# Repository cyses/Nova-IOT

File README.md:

<!DOCTYPE html><html><head><meta charset="utf-8"></head><body id="preview">
<h1 class="code-line" data-line-start=0 data-line-end=1>NovaIoT Cookbook</h1>

<p class="has-line-data" data-line-start="5" data-line-end="6">NovaIoT is an open-source framework that is made for spreading LoRa Sensors all over the world. NovaIoT package consists of two main parts:</p>
<ul>
<li class="has-line-data" data-line-start="6" data-line-end="7">The Hardware design for LoRa modules</li>
<li class="has-line-data" data-line-start="7" data-line-end="8">The Software design for LoRa sensors.</li>
<li class="has-line-data" data-line-start="8" data-line-end="10">And a little bit Magic :)</li>
</ul>
<h1 class="code-line" data-line-start=10 data-line-end=11>New Features!</h1>
<ul>

<li class="has-line-data" data-line-start="12" data-line-end="13">You can visualize the sensor data in the GUI app with a RestFull API.</li>
</ul>
<p class="has-line-data" data-line-start="16" data-line-end="17">You can also:</p>
<ul>
<li class="has-line-data" data-line-start="17" data-line-end="18">Use the hardware design and print the PCB.</li>
<li class="has-line-data" data-line-start="18" data-line-end="19">With required components for PCB you can complete the sensor at all.</li>
<li class="has-line-data" data-line-start="19" data-line-end="20">You can use any IP67 case for the sensor. (We are going to upload the IP67 design soon if you want to use a ready one!)</li>
<li class="has-line-data" data-line-start="20" data-line-end="21">You can integrate the sensor on our server software. (which would be online soon!)</li>
<li class="has-line-data" data-line-start="21" data-line-end="22">You can use our GUI in order to visualize the sensor data (just think like mqtt)</li>
</ul>
<p class="has-line-data" data-line-start="24" data-line-end="25">Here there are several things that we need to mention before we start!</p>
<blockquote>
<p class="has-line-data" data-line-start="26" data-line-end="32">Our primer aim is to spread this LoRa sensors all over the world fastly.<br>
We really believe in the power of open-source<br>
and we are always open to commits and suggestions!<br>
Please feel free if you have an idea for making any of these technologies better<br>
We are ready to hear and make the system better!<br>
or if you just want to use the design, you are very welcome. But do not forget that, it is free for NON-COMMERCIAL use!</p>
</blockquote>
<h3 class="code-line" data-line-start=34 data-line-end=35>Tech</h3>
<p class="has-line-data" data-line-start="36" data-line-end="37">First lets mention what components should you use. The components in the lists required very hard work and took a lot of time in order to find them.</p>
<ul>
<li class="has-line-data" data-line-start="38" data-line-end="39">STM32L072CZT6 - The main microprocessor that we used in our PCB</li>
<li class="has-line-data" data-line-start="39" data-line-end="40">SX1276IMLTRT - the core component for LoRa</li>
<li class="has-line-data" data-line-start="40" data-line-end="41">Li/SOCL2 4000 mAH 3.6v connector 2.54mm Two batteries side by side with protection - this is the magic battery. :)</li>
<li class="has-line-data" data-line-start="41" data-line-end="42">RFM95W-868 - the integrated LoRa module</li>
</ul>
<h3 class="code-line" data-line-start=45 data-line-end=46>Installation</h3>
<p class="has-line-data" data-line-start="47" data-line-end="49">We are changing our software infrastructure in docker based containers. But of course that would take time. Until that time you can use our PHP applications for GUI and server. You can ask us anything if you tackle in somewhere.<br>
The requirements for now are;</p>
<ul>
<li class="has-line-data" data-line-start="50" data-line-end="51">PHP 7.2 +</li>
<li class="has-line-data" data-line-start="51" data-line-end="52">Apache</li>
<li class="has-line-data" data-line-start="52" data-line-end="53">MySQL</li>
</ul>
After completing the setup of docker infrastructure, you would be run the environment as
<pre><code class="has-line-data" data-line-start="56" data-line-end="60" class="language-sh">$ <span class="hljs-built_in">docker</span> compose up

</code></pre>
<h3 class="code-line" data-line-start=63 data-line-end=64>Todos</h3>
<ul>
<li class="has-line-data" data-line-start="65" data-line-end="66"><em>Docker container</em></li>
<li class="has-line-data" data-line-start="66" data-line-end="68">Improvements in hardware design in order to make the PCB smaller</li>
</ul>
<h2 class="code-line" data-line-start=68 data-line-end=70>License</h2>
<p class="has-line-data" data-line-start="71" data-line-end="72">MIT</p>
<p class="has-line-data" data-line-start="74" data-line-end="75"><strong>Free Software, Hell Yeah!</strong></p>
</body></html>

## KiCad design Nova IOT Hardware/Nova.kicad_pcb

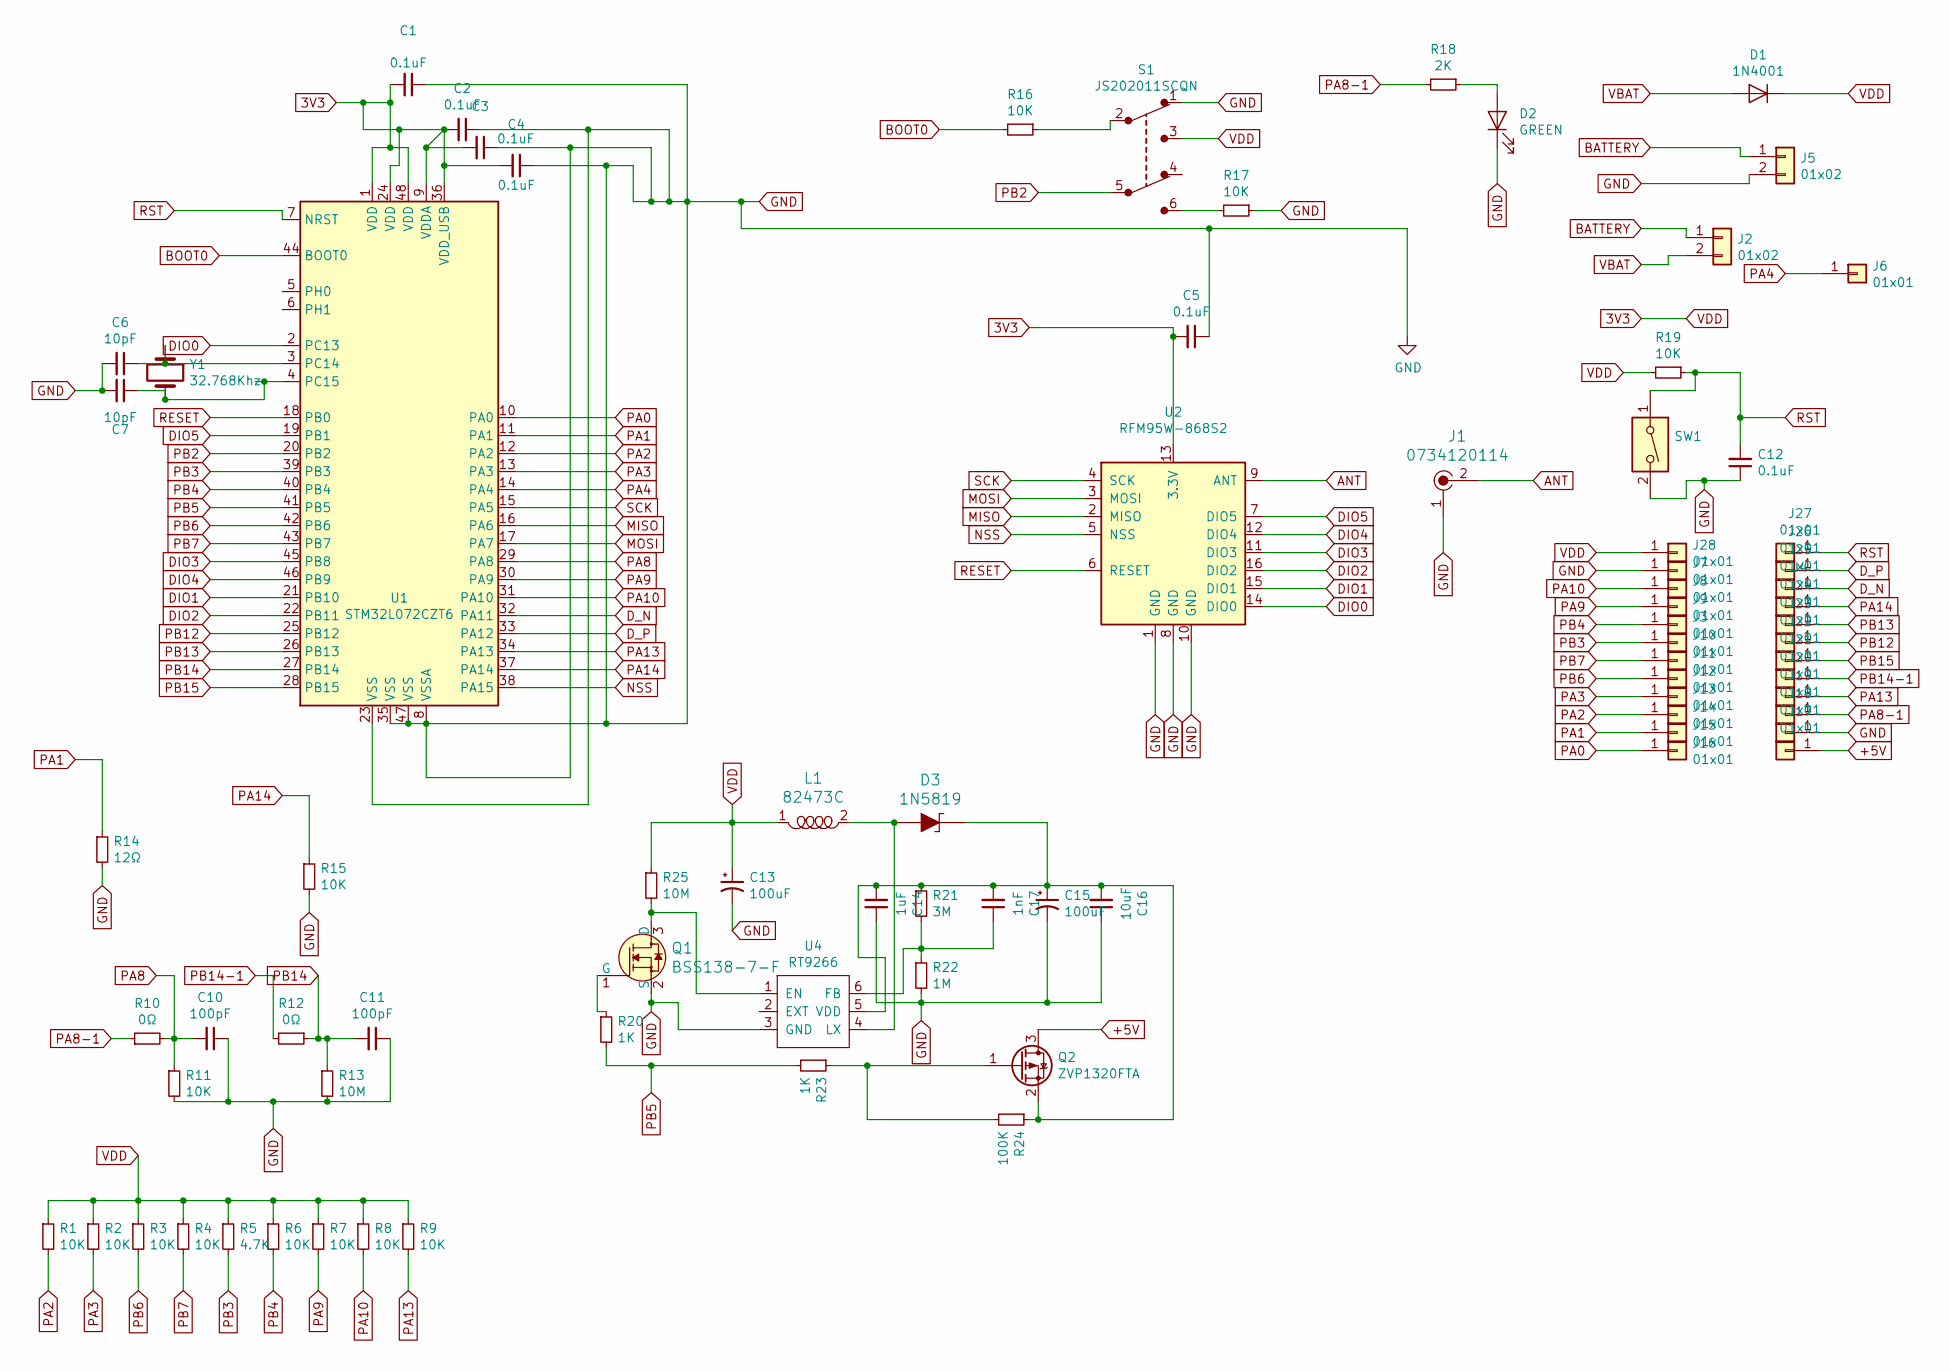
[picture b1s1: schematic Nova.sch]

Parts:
C1, C2, C3, C4, C5, C12: 0.1uF; 0603
C6, C7: 10pF; 0603
C10, C11: 100pF; 0603
C13, C15: 100uF; 0805
C14: 1uF; 0603
C16: 10uF; 0603
C17: 1nF; 0603
D1: 1N4001; D_DO-41_SOD81_P10.16mm_Horizontal
D2: GREEN; 0603
D3: 1N5819; DO-41; MPN 1N5819; Digi-Key_PN 1N5819FSCT-ND
J1: 0734120114; Molex_734120114_UMC_RF_CONN_Vertical; MPN 0734120114; Digi-Key_PN WM3894CT-ND
J2, J5: 01x02; PinHeader_1x02_P2.54mm_Vertical
J3, J4, J6, J7, J8, J9, J10, J11, J12, J13, J14, J15, J16, J17, J18, J19, J20, J21, J22, J23, J24, J25, J26, J27, J28: 01x01; PinHeader_1x01_P2.54mm_Vertical
L1: 82473C; 1210; MPN 82473C; Digi-Key_PN 811-2477-1-ND
Q1: BSS138-7-F; SOT-23-3; MPN BSS138-7-F; Digi-Key_PN BSS138-FDICT-ND
Q2: ZVP1320FTA; SOT-23
R1, R2, R3, R4, R6, R7, R8, R9, R11, R15, R16, R17, R19: 10K; 0603
R5: 4.7K; 0603
R10, R12: 0Ω; 0603
R13, R25: 10M; 0603
R14: 12Ω; 0603
R18: 2K; 0603
R20, R23: 1K; 0603
R21: 3M; 0603
R22: 1M; 0603
R24: 100K; 0603
S1: JS202011SCQN; Switch_Slide_JS202011SCQN; MPN JS202011SCQN; Digi-Key_PN 401-2002-1-ND
SW1: SW; Switch_Tactile_SMD_6x6mm
U1: STM32L072CZT6; LQFP-48_7x7mm_P0.5mm
U2: RFM95W-868S2; XCVR_RFM95W-868S2
U4: RT9266; SOT-23-6
Y1: 32.768Khz; SMD-2_3.2x1.5mm

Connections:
3V3: C1.2, C2.2, C3.2, C4.2, C5.2, C13.1, D1.1 (K), J28.1, L1.1, R1.1, R2.1, R3.1, R4.1, R5.1, R6.1, R7.1, R8.1, R9.1, R19.2, R25.1, S1.3, U1.1 (VDD), U1.9 (VDDA), U1.24 (VDD), U1.36 (VDD_USB), U1.48 (VDD), U2.13 (3.3V)
+5V: J17.1, Q2.3 (D)
ANT: J1.2, U2.9 (ANT)
BATTERY: J2.1, J5.1
BOOT0: R16.2, U1.44 (BOOT0)
DIO0: U1.2 (PC13), U2.14 (DIO0)
DIO1: U1.21 (PB10), U2.15 (DIO1)
DIO2: U1.22 (PB11), U2.16 (DIO2)
DIO3: U1.45 (PB8), U2.11 (DIO3)
DIO4: U1.46 (PB9), U2.12 (DIO4)
DIO5: U1.19 (PB1), U2.7 (DIO5)
D_N: J25.1, U1.32 (PA11)
D_P: J26.1, U1.33 (PA12)
GND: C1.1, C2.1, C3.1, C4.1, C5.1, C6.2, C7.2, C10.1, C11.1, C12.1, C13.2, C14.1, C15.2, C16.1, D2.1 (K), J1.1, J5.2, J7.1, J18.1, Q1.2 (S), R11.2, R13.2, R14.2, R15.2, R17.1, R22.2, S1.1, SW1.2, U1.8 (VSSA), U1.23 (VSS), U1.35 (VSS), U1.47 (VSS), U2.1 (GND), U2.8 (GND), U2.10 (GND), U4.3 (GND)
MISO: U1.16 (PA6), U2.2 (MISO)
MOSI: U1.17 (PA7), U2.3 (MOSI)
NSS: U1.38 (PA15), U2.5 (NSS)
unnamed: C6.1, U1.3 (PC14), Y1.1
unnamed: C7.1, U1.4 (PC15), Y1.2
unnamed: C14.2, C15.1, C16.2, C17.2, D3.K, Q2.2 (S), R21.1, R24.1, U4.5 (VDD)
unnamed: C17.1, R21.2, R22.1, U4.6 (FB)
unnamed: D2.2 (A), R18.1
unnamed: D3.A, L1.2, U4.4 (LX)
unnamed: Q1.1 (G), R20.1
unnamed: Q1.3 (D), R25.2, U4.1 (EN)
unnamed: Q2.1 (G), R23.1, R24.2
unnamed: R16.1, S1.2
unnamed: R17.2, S1.6
PA0: J16.1, U1.10 (PA0)
PA1: J15.1, R14.1, U1.11 (PA1)
PA2: J14.1, R1.2, U1.12 (PA2)
PA3: J13.1, R2.2, U1.13 (PA3)
PA4: J6.1, U1.14 (PA4)
PA8: C10.2, R10.2, R11.1, U1.29 (PA8)
PA8-1: J19.1, R10.1, R18.2
PA9: J9.1, R7.2, U1.30 (PA9)
PA10: J8.1, R8.2, U1.31 (PA10)
PA13: J20.1, R9.2, U1.34 (PA13)
PA14: J4.1, R15.1, U1.37 (PA14)
PB2: S1.5, U1.20 (PB2)
PB3: J10.1, R5.2, U1.39 (PB3)
PB4: J3.1, R6.2, U1.40 (PB4)
PB5: R20.2, R23.2, U1.41 (PB5)
PB6: J12.1, R3.2, U1.42 (PB6)
PB7: J11.1, R4.2, U1.43 (PB7)
PB12: J23.1, U1.25 (PB12)
PB13: J24.1, U1.26 (PB13)
PB14: C11.2, R12.1, R13.1, U1.27 (PB14)
PB14-1: J21.1, R12.2
PB15: J22.1, U1.28 (PB15)
RESET: U1.18 (PB0), U2.6 (RESET)
RST: C12.2, J27.1, R19.1, SW1.1, U1.7 (NRST)
SCK: U1.15 (PA5), U2.4 (SCK)
VBAT: D1.2 (A), J2.2

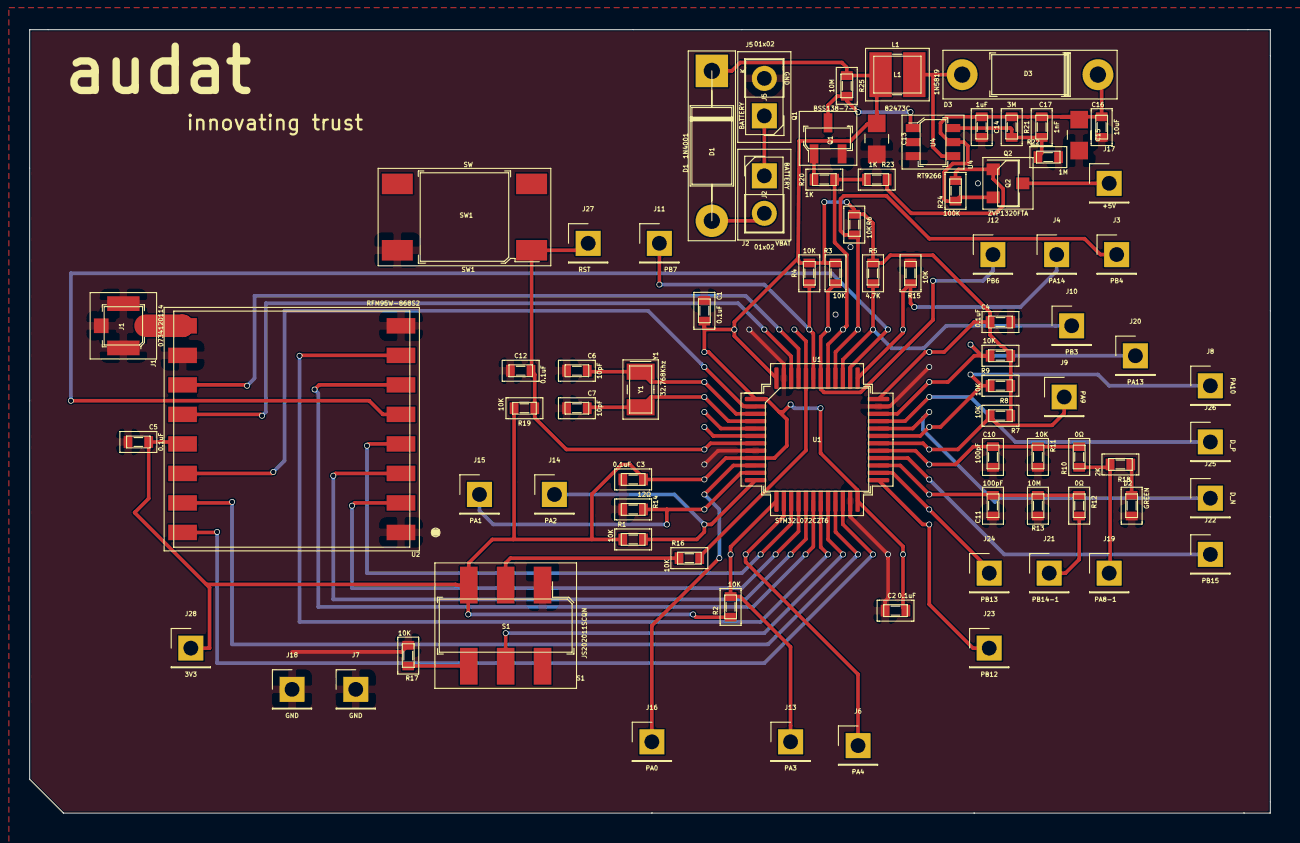
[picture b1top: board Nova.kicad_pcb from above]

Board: 2 copper layers, 84.1 x 53.1 mm, 80 parts (0 on the bottom side), 54 nets.

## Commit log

2020-03-27 Create Nova-IOT
2020-03-27 Add files Nova-IOT
2020-03-27 Change files Nova-IOT
